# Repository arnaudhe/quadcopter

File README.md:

# Quadcopter

DIY quadcopter based on ESP32-WROOM

## Overview

### Architecture overview

```mermaid
  flowchart LR;
    subgraph QUADCOPTER
      BATTERY--supply-->Flight_controller
      BATTERY--supply-->GIMBAL
      HCSR04<--pulse-->ESP32
      subgraph Flight_controller
        MPU6050--I2C-->ESP32
        HMC5883L--I2C-->ESP32
        BMP280--I2C-->ESP32
        ESP32--DSHOT-->ESC
        ESP32--SPI-->SI4432
      end
      subgraph Motors
        ESC--3-->FRONT_RIGHT_MOTOR
        ESC--3-->FRONT_LEFT_MOTOR
        ESC--3-->REAR_RIGHT_MOTOR
        ESC--3-->REAR_LEFT_MOTOR
      end
      subgraph Video
        direction TB
        ESP32--PWM-->GIMBAL
        ESP32--TCP-->CAMERA
        CAMERA--Analog-->VIDEO_TX
        GIMBAL--supply-->VIDEO_TX
      end
      GPS--UART-->ESP32
    end
      subgraph Base_Station
        XBOX_REMOTE--USB-->LAPTOP
        LAPTOP<--USB-->RADIO_DONGLE
        VIDEO_RX--USB-->LAPTOP
      end
      RADIO_DONGLE-.433 MHz FSK.->SI4432
      LAPTOP-.WIFI.->ESP32
      VIDEO_TX-.5,8GHz.->VIDEO_RX
```

### Sensors

* Attitude sensing is based on MPU6050 (accelerometer + gyroscope) and HMC5883L (magnetometer), computed through a [Madgwick Filter](https://x-io.co.uk/open-source-imu-and-ahrs-algorithms/)
* Height sensing is based on vertical linear acceleration (output of attitude filter), a BMP180 (barometer) and a HCSR04 (ultrasound range sensor), computed through a [Kalman filter](https://en.wikipedia.org/wiki/Kalman_filter)
* Position sensing is base on horizontal linear acceleration (output of attitude filter) and a GPS, computed through a Kalman filter [Kalman filter](https://en.wikipedia.org/wiki/Kalman_filter)

cf. [documents](https://github.com/arnaudhe/quadcopter/tree/master/documents) for more details

### Controllers

* Attitude controller (manual mode) is based on a 4-dimensions [PID](https://en.wikipedia.org/wiki/PID_controller) (roll, pitch, yaw, height)
* Position controller (autonomous mode) is based on a 3-dimensions [PID](https://en.wikipedia.org/wiki/PID_controller) (x, y, z) which drives attitude controller

BLDC motors control is based on a commercial 4-in-1 ESC (electronic speed controller)

cf. [documents](https://github.com/arnaudhe/quadcopter/tree/master/documents) for more details

### Camera

The quadcopter is designed to support a [YI action camera](https://www.yitechnology.com/yi-action-camera), hold on a [2D Gimbal](https://hobbyking.com/fr_fr/tarot-t-2d-v2-xiaomi-yi-sports-camera-brushless-camera-gimbal-and-zyx22-controller.html).

The camera has:
* A TCP interface which supports json commands (take a picture, start recording, list files, ...)
* A streaming RTSP server which can be used for live video preview

The gimbal angles can be driven by the ESP32 through a serial interface.

### Communication

Communication between base station (computer or remote) is based on a shared data model, definied in a json file.

The data model ressources are implemented by the quadcopter and can be read/written/notified via:
* a json protocol (better for debug, high bandwith medium)
* a binary protocol (better for release, low bandwidth medium)

Two communications media are supported by the quadcopter:
* wifi (low range, hight bandwidth)
* FSK (longer range, low bandwidth)

```mermaid
  flowchart TD;
      subgraph Flight controller
      ESP32<-->WIFI;
      ESP32<-->RADIO;
      end
      WIFI--TCP/JSON-->CAMERA;
      CAMERA--Analog Video-->VTX
      VTX-->BASE_STATION
      WIFI<--UDP/JSON-->BASE_STATION
      RADIO<--FSK/BINARY-->BASE_STATION
```

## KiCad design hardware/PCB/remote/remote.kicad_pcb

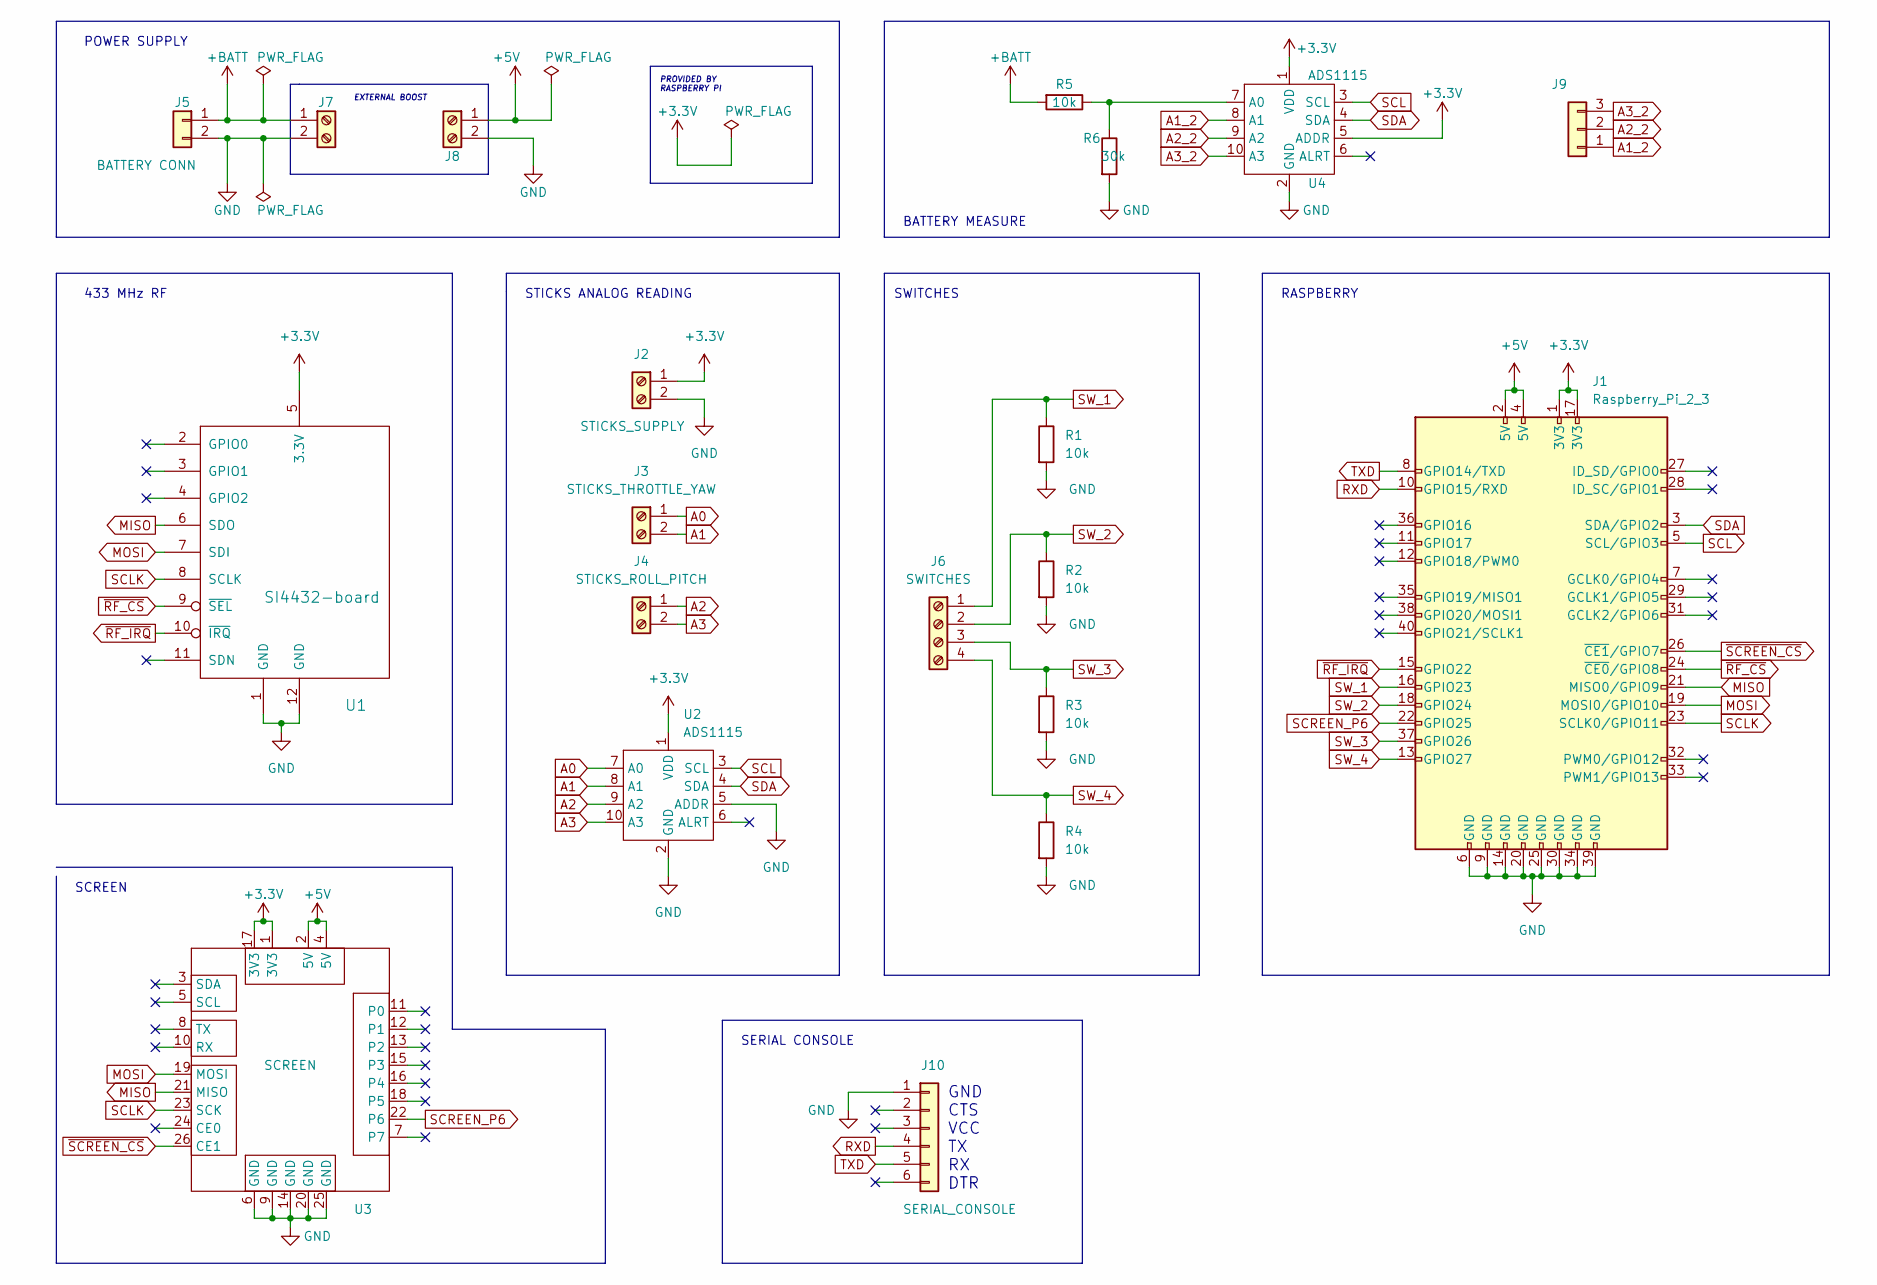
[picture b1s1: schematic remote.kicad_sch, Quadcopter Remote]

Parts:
J1: Raspberry_Pi_2_3; Raspberry_Pi_Zero_Socketed_THT_FaceDown_MountingHoles
J2: STICKS_SUPPLY; TerminalBlock_bornier-2_P5.08mm
J3: STICKS_THROTTLE_YAW; TerminalBlock_bornier-2_P5.08mm
J4: STICKS_ROLL_PITCH; TerminalBlock_bornier-2_P5.08mm
J5: BATTERY CONN; BATTERY_CHARGER
J6: SWITCHES; TerminalBlock_bornier-4_P5.08mm
J7, J8, J9: (no value)
J10: SERIAL_CONSOLE; PinHeader_1x06_P2.54mm_Vertical
R1, R2, R3, R4, R5: 10k; R_1206_3216Metric_Pad1.30x1.75mm_HandSolder
R6: 30k; R_1206_3216Metric_Pad1.30x1.75mm_HandSolder
U1: SI4432-board
U2, U4: ADS1115
U3: SCREEN; PinHeader_2x13_P2.54mm_Vertical

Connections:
+3V3: J1.1 (3V3), J1.17 (3V3), J2.1, U1.5 (3.3V), U2.1 (VDD), U3.1 (3V3), U3.17 (3V3), U4.1 (VDD), U4.5 (ADDR)
+5V: J1.2 (5V), J1.4 (5V), J8.1, U3.2 (5V), U3.4 (5V)
+BATT: J5.1, J7.1, R5.2
A0: J3.1, U2.7 (A0)
A1: J3.2, U2.8 (A1)
A1_2: J9.1, U4.8 (A1)
A2: J4.1, U2.9 (A2)
A2_2: J9.2, U4.9 (A2)
A3: J4.2, U2.10 (A3)
A3_2: J9.3, U4.10 (A3)
GND: J1.6 (GND), J1.9 (GND), J1.14 (GND), J1.20 (GND), J1.25 (GND), J1.30 (GND), J1.34 (GND), J1.39 (GND), J2.2, J5.2, J7.2, J8.2, J10.1, R1.2, R2.2, R3.2, R4.2, R6.2, U1.1 (GND), U1.12 (GND), U2.2 (GND), U2.5 (ADDR), U3.6 (GND), U3.9 (GND), U3.14 (GND), U3.20 (GND), U3.25 (GND), U4.2 (GND)
MISO: J1.21 (MISO0/GPIO9), U1.6 (SDO), U3.21 (MISO)
MOSI: J1.19 (MOSI0/GPIO10), U1.7 (SDI), U3.19 (MOSI)
unnamed: R5.1, R6.1, U4.7 (A0)
RXD: J1.10 (GPIO15/RXD), J10.4
SCL: J1.5 (SCL/GPIO3), U2.3 (SCL), U4.3 (SCL)
SCLK: J1.23 (SCLK0/GPIO11), U1.8 (SCLK), U3.23 (SCK)
SCREEN_P6: J1.22 (GPIO25), U3.22 (P6)
SDA: J1.3 (SDA/GPIO2), U2.4 (SDA), U4.4 (SDA)
SW_1: J1.16 (GPIO23), J6.1, R1.1
SW_2: J1.18 (GPIO24), J6.2, R2.1
SW_3: J1.37 (GPIO26), J6.3, R3.1
SW_4: J1.13 (GPIO27), J6.4, R4.1
TXD: J1.8 (GPIO14/TXD), J10.5
~RF_CS: J1.24 (~CE0/GPIO8), U1.9 (~SEL)
~RF_IRQ: J1.15 (GPIO22), U1.10 (~IRQ)
~SCREEN_CS: J1.26 (~CE1/GPIO7), U3.26 (CE1)

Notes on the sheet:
SERIAL CONSOLE
GND CTS VCC TX RX DTR
EXTERNAL BOOST
SWITCHES
BATTERY MEASURE
PROVIDED BY RASPBERRY PI
STICKS ANALOG READING
SCREEN
RASPBERRY
POWER SUPPLY
433 MHz RF

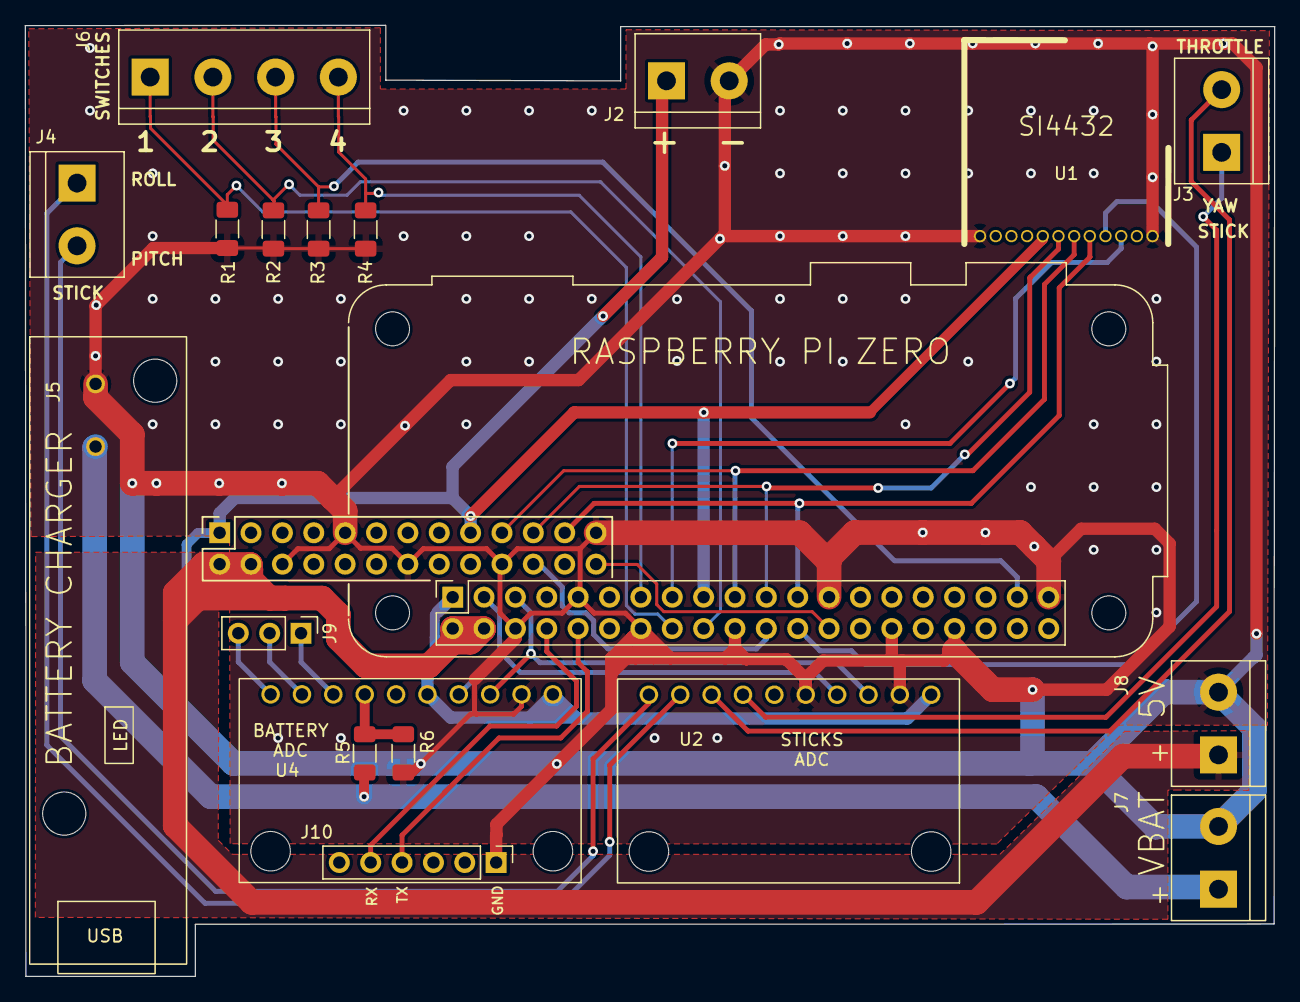
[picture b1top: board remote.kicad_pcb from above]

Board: 2 copper layers, 101.2 x 77.0 mm, 20 parts (1 on the bottom side), 27 nets.

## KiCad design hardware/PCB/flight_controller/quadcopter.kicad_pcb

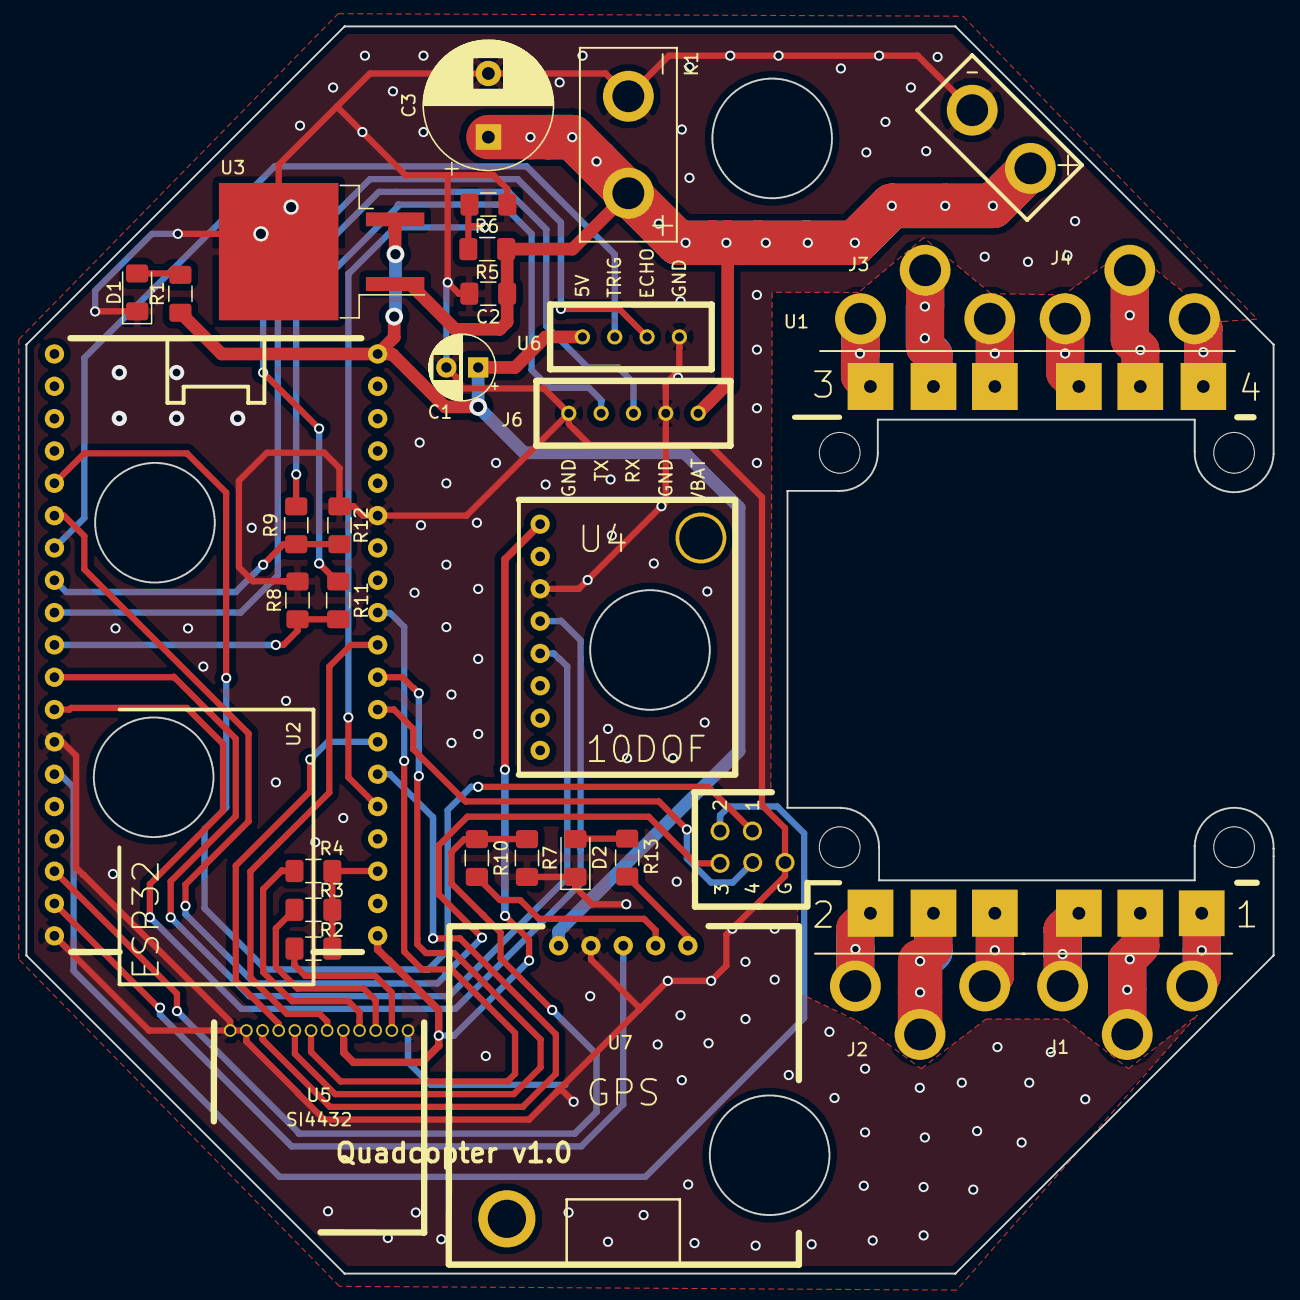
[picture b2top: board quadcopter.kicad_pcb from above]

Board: 2 copper layers, 98.0 x 98.0 mm, 31 parts (0 on the bottom side), 44 nets.

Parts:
C1: 22u; CP_Radial_D5.0mm_P2.50mm
C2: 470n; C_1206_3216Metric_Pad1.42x1.75mm_HandSolder
C3: 470u; CP_Radial_D10.0mm_P5.00mm
D1, D2: LED; LED_1206_3216Metric_Pad1.42x1.75mm_HandSolder
J1, J2, J3, J4: CONN-MOTOR; motor-connector
J6: GIMBAL
K1: BATTERY; battery-connector
R1, R13: 1k; R_1206_3216Metric_Pad1.42x1.75mm_HandSolder
R2, R3, R4: 0; R_1206_3216Metric_Pad1.42x1.75mm_HandSolder
R5: 30k; R_1206_3216Metric_Pad1.42x1.75mm_HandSolder
R6, R10, R11, R12: 10k; R_1206_3216Metric_Pad1.42x1.75mm_HandSolder
R7, R8, R9: 20k; R_1206_3216Metric_Pad1.42x1.75mm_HandSolder
U1: ESC
U2: ESP-WROOM-32-board; ESP32-VROOM-board
U3: LM2936-5.0; TO-263-2
U4: 10DOF
U5: SI4432-board
U6: HC-SR04
U7: GPS

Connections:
+3V3: U2.1, U4.1, U5.5
+5V: C1.1, R1.1, U2.19, U3.3, U6.1, U7.1
+BATT: C2.1, C3.1, J6.1, K1.1, R5.1, U1.1, U3.1
ESC_CMD1: U1.16, U2.24
ESC_CMD2: U1.17, U2.33
ESC_CMD3: U1.18, U2.25
ESC_CMD4: U1.19, U2.8
GIMBAL_RX: J6.3, U2.28
GIMBAL_TX: R9.1, R12.2, U2.27
GND: C1.2, C2.2, C3.2, D1.1, D2.1, J6.2, J6.5, K1.2, R6.2, R7.2, R8.2, R9.2, U1.2, U1.15, U2.14, U2.32, U2.38, U3.2, U4.3, U5.1, U5.11, U5.12, U6.4, U7.4
GPS_RX: U2.37, U7.3
GPS_TX: R7.1, R10.2, U2.36
HC-SR04_ECHO: R8.1, R11.2, U2.29
HC-SR04_TRIG: U2.26, U6.2
MEAS_BATT: R5.2, R6.1, U2.5
unnamed: D1.2, R1.2
unnamed: D2.2, R13.2
unnamed: J1.1, U1.3
unnamed: J1.2, U1.4
unnamed: J1.3, U1.5
unnamed: J2.1, U1.6
unnamed: J2.2, U1.7
unnamed: J2.3, U1.8
unnamed: J3.1, U1.9
unnamed: J3.2, U1.10
unnamed: J3.3, U1.11
unnamed: J4.1, U1.12
unnamed: J4.2, U1.13
unnamed: J4.3, U1.14
unnamed: J6.4, R12.1
unnamed: R2.1, U5.2
unnamed: R3.1, U5.3
unnamed: R4.1, U5.4
unnamed: R10.1, U7.2
unnamed: R11.1, U6.3
unnamed: R13.1, U7.5
SCK: U2.9, U5.8
SCL: U2.31, U4.4
SDA: U2.30, U4.5
SDI: U2.11, U5.7
SDO: U2.10, U5.6
SI4432_GPIO: R2.2, R3.2, R4.2, U2.3
~SI4432_IRQ: U2.6, U5.10
~SI4432_SEL: U2.7, U5.9

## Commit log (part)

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2021-11-03 [periodic task] Add log with actual measured task frequency every 10 sec
2021-11-03 [pulse] Fix timer configuration
2021-11-03 [.gitignore] Add pycache
2021-11-03 [base station logger] Convert logger to a class
2021-11-03 [base station] Deep refactoring to have gui, logging and xbox controller modules
2021-11-04 [tests] Add gps and filters testing notebooks
2021-11-11 [UART] Use project custom queue
    and move queue template functions into header file, add a typedef for freeRTOS queue handle to avoid using it outside this wrapper, add a constructor based on a queue handle, add an "empty" function 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
2021-11-11 [DATA] Use filesystem to read data model
    and upload the storage image folder each time the ESP32 is flashed
2021-11-11 [GPS] Add serial into main
    Opening port and configuring pattern detection (no callback for now)
2021-11-11 [NMEA] Add NMEA controller into main
    and plug it with registry and uart pattern detection callback
2021-11-11 [NMEA] Add new NMEA controller class
    In order to parse NMEA sequence and then store GPS data in the registry
2021-11-11 [LOG] Add verbose logging
    and fix "debug" prefix (W -> D)
2021-11-11 [REGISRTY] Add double type support
    Base station, data model converter, registry and json protocol source code upgrade
2021-11-11 [UART] Use project custom logging
    and increase task stack to handle this new logging
2021-11-11 [NMEA] Use project custom logging
    and increase task stack to handle this new logging
2021-11-11 [data model] update build system to use common data_model
2021-11-11 [NMEA] Move parsing to dedicated class in utils
2021-11-11 [GPS] Move NMEA_controller to GPS in HAL layer
2021-11-11 [GPS] Init UART and start pattern matcher from GPS class
2021-11-11 [GPS] Fill data model resources with parsed NMEA data
2021-11-11 [UART] Formatting
2021-11-11 Fix build in data recording mode
2021-11-11 [motors] Add dedicated motor_controller for manual motor control
2021-11-11 [PID] Increase D-term low-pass filtering
2021-11-11 [main] Set explicit control.phase registry initialization
2021-11-11 [rate ctrl] PID tuning
2021-11-18 [setup] init submodules in setup
2021-11-18 [data model] Data model reworking
2021-11-18 [data model] Add sensors to data model
2021-11-18 [base station] Fix displayed widgets value after loading
2021-11-18 [base station] Fix return type on read command error
2021-11-19 [pid] remove debug as it is replaced by telemetry
2021-11-19 [data model] Add string ressource support
2021-11-19 [UART] Improve naming, formatting and log levels
2021-11-19 [uart] fix GPS decoding error by preventing flushing received following bytes at pattern detection
2022-01-05 [telemetry] add telemetry sending over UDP
2022-01-05 [base station] connect telemetry and scope to make some magic
2022-01-14 [scope] Improve config loading
2022-01-14 [sdkconfig] Fix monitor baudrate to 921600
2022-01-14 [sdkconfig] Increase RTOS timer service queue length
2022-01-14 [task] Distribute tasks to both core 0 and core 1
2022-01-14 [gyro] Move gyro calibration sequence after init (when drone don't move)
2022-01-14 [uart] tune queues length and fix pattern detector
2022-01-14 [height ctlr] Fix bad registry ressource key
2022-01-14 [data model] Expose PID commands in data model
2022-01-14 [base station] Add scope configs
2022-01-14 [vscode] Fix build problem matcher config
2022-01-24 Remove non real-time critical functions from RAM
2022-01-24 [registry] Add direct handle to resource getter for faster access, without key lookup
2022-01-24 [attitude ctrl] Fix invalid min and max PID output commands
2022-01-24 [PID] Replace error derivate by input derivate to ignore setpoints steps
2022-01-24 [telemetry] Bulk telemetry data into one UDP datagram if period is too fast
2022-01-24 [attitude / rate] PID tuning
2022-01-24 [vscode] Use serial port from settings for flash and monitor tasks
2022-01-24 [scope] Add sensors (gyroscope and accelerometer) telemetry config
2022-01-27 [scope] Use more colors
2022-01-27 [base station] Split in modules and add option to write telemetry data to file
2022-01-27 [attitude ctrl] Update tuning
2022-01-27 [base station] Update python requirements
2022-01-27 [rate ctlr] Set static RPM notch filter
2022-01-27 [rate ctlr] Fix bad gyro calibration correction
2022-01-27 [filters] Update slew rate filter
2022-01-27 [rate ctlr] Add accelero bias correction with calibration
2022-01-27 [filters] Add unit tests
2022-01-27 [env] Add base_station folder to dev environment path
2022-01-27 [PID] Reduce default (rate control) min and max commands
2022-01-27 [euler observer] Increase observer gain for faster drift correction
2022-01-27 [height ctlr] First approximative tuning
2022-01-27 [height ctlr] Fill barometer and ultrasound measures in registry for telemetry
2022-02-01 [cmake] remove trailing spaces
2022-02-01 [PID] Add state reset method and call it when controllers are disabled
2022-02-01 [height ctlr] TEMPORARY - Use ultrasound sensor height instead of Kalman filter output
2022-02-01 [rate ctlr] Use static gyro calibration
2022-02-01 [RC] Add basic continuous stream radio control over UDP
2022-02-01 [scope] Enable FFT to gyro to measure filters effets
2022-02-05 [SPI] First implementaion
2022-02-05 [base station] Exit with error if remote asked but not plugged
2022-02-05 [radio command] Set yaw and throttle commands received on rc
2022-02-11 [GPS] Fix memory leak in NMEA parser
2022-02-13 [base station] Add basic GUI generation script with video stream display
2022-02-16 [GPIO] Fix gpio init for pins 33-36
2022-02-16 [SI4432] Improve driver with IRQ management
2022-02-16 [main] Add FSK reception in main loop
2022-02-18 [HCSR04] Stop limiting the sensor output to 1m
2022-02-18 [BMP280] Reduce low-pass filter
2022-02-18 [height observer] Remove zero-velocity detector
2022-02-18 [height observer] Reduce output order to 1 (only barometer)
2022-02-18 [scope] Update height scope config
2022-02-18 [docs] Add SI4432 datasheets
2022-03-01 [tools] Add requirements file for python package dependencies
2022-03-01 [vscode] Add tools folder in workspace
2022-03-01 [battery] Add periodic battery monitoring
2022-03-03 [SI4432] Tune config for working RX
2022-03-03 [SI4432] Add RSSI reading function
2022-03-03 [base station] Add radio dongle module
2022-03-03 [battery] tune ADC measure after divider increased
2022-03-03 [battery] Increase battery voltage log resolution
2022-03-08 [protocol] Move binary protocol encoder/decoder to base station
2022-03-08 [base station] Rework architecture to work over a udp or radio broker
2022-03-08 [data model] Fix some binary ressource ids
2022-03-08 [soft] Create dedicated class for periodic heartbeat
2022-03-10 [base station] Add some docstrings
2022-03-10 [Heartbeat] Use radio broker with proper channel for heartbeat sending
2022-03-10 [radio command] Make UDP reception non-blocking to enable listening on radio
2022-03-10 [broker] Centralize broker channels and use thoses definitions for UDP
2022-03-10 [radio command] Improve sticks reading and add non-linear rates
2022-03-10 [radio] Stabilize python radio driver and broker
2022-03-10 [height control] Replace default mode from manual to speed control
2022-03-10 [Si4432] Reduce log verbosity on frame receiving
2022-03-10 [attitude ctrl] Update PIDs tuning with new propellers
2022-03-10 [README] Replace ASCII-scheme with mermaid
2022-03-10 [README] Update architecture schema
2022-03-12 [README] Add architecture overview graph
2022-03-14 [scope] Add vertical speed to height scope config
2022-03-26 [radio] Add CRC16 frame integrity check
2022-03-26 [base station] Fix periodic worker instanciation
2022-03-26 [height observer] Tuning & restoring zero velocity detector to improve stability
2022-03-27 [base station] Add method to get radio link quality in percents
2022-03-31 [radio] Remove broker mechanisms from radio and convert to lower level abstraction layer
2022-03-31 [udp] Convert UDP to lower level os abstraction layer
2022-03-31 [crc16] Add method to update with one-byte input
2022-03-31 [broker] Create broker for UDP and radio communication channels multiplexing
2022-03-31 [Heartbeat] Use broker instead of out-of-date Udp server and radio broker
2022-03-31 [data recorder] Move to workers folder
2022-03-31 [json protocol] make it stateless by removing registration to out-of-date UDP server
2022-03-31 [binary protocol] Add binary data model protocol manager
2022-03-31 [data model ctrl] Centralize json and binary requests handling in ctlr which relies on broker
2022-03-31 [main] Suppress unused variables warnings
2022-04-01 [tests] Refactor soft tests and add binary protocol tests
2022-04-01 [tasks] tune priority and stack sizes
2022-04-01 [Heartbeat] Increase period to 3 sec to avoid radio collisions
2022-04-01 [protocol] Fix python float and double variables encoding
2022-04-01 [radio] Remove link quality log on each reception
2022-04-01 [radio] Add delay before exiting TX to avoid CRC errors
2022-04-02 [status] Remove not used status declaration
2022-04-02 [byte array] Add clear and replace data methods
2022-04-03 [base station] Display camera properties in GUI
2022-04-03 [wifi] Fix wifi state mangement
2022-04-03 [barometer] increase stack size
2022-04-03 [camera] Add yi action camera HAL implementation (tcp over wifi)
2022-04-03 [code] Update workspace settings
2022-04-03 [tcp] Add os-level tcp abstraction class
2022-05-01 Move base station
2022-05-01 Move data model
2022-05-01 Move 3D
2022-05-01 Move flight_controller PCB
2022-05-01 Move test & tools
2022-05-01 Move sizing
2022-05-01 [PCB] Add remote PCB v1.0
2022-05-01 Move env
2022-05-01 [vscode] Improve C/C++ config
2022-05-01 [GPS] Fix missing initializer warning
2022-05-02 [3D] Add quadcopter antennas holders
2022-05-02 [3D] Add remote top
2022-05-19 Add radio_command skeleton
2022-05-19 Add radio_command to code workspace
2022-05-24 [radio command] Add iio ADC abstraction layer
2022-05-24 [radio command] Fix sticks ADC channels
2022-05-24 [radio command] Fix I2C port
2022-05-24 [radio command] Add I2C bulk registers read and write method
2022-05-24 [radio command] Fix SPI unused include
2022-05-24 [radio command] Update method call to get sticks command
2022-05-24 [radio command] Fix buttons GPIO mapping
2022-05-24 [radio command] Add ADS1115 ADC over I2C implementation
2022-05-24 [base station] Fix out-of-date methods call in radio test snippet
2022-05-24 [radio command] Add basic periodic radio sending
2022-05-30 [radio_command] Add radio layer and basic implementation
2022-06-11 [3D] Add landing system pieces
2022-06-17 [rc] Import libjpeg dependency in sysroot
2022-06-17 [rc] Add jpeg decoding class based on libjpeg
2022-06-17 [rc] Add framebuffer abstraction class to display image on screen
2022-06-17 [rc] Add task abstraction class based on pthread dep
2022-06-17 [rc] Start parallel video, rc and battery workers at startup
2022-06-17 [rc] Fix gpio shared memory access denied permission
2022-06-17 [rc] open I2C device in constructor instead of dedicated method
2022-06-17 [rc] Remove attribute initialization in class declaration
2022-06-17 [rc] Add video feedback applicative worker
2022-06-17 [rc] Change vscode C/C++ compiler path on linux
2022-06-17 [3D] Add remote backcover
2022-06-17 [3D] Add remote usb hub and batery support
2022-06-17 Align radio frames staructure with length
2022-06-19 [rc] Add PixMap mathods to display text, rectangle, and color filling
2022-06-19 [rc] Enter in range test mode when pressing both bottom buttons at startup
2022-06-19 [flight controller] Add state machine utility base class
2022-06-19 [fc] Send status through rc channel every second
2022-06-19 [flight controller] Add periodic task method to on-demand execute run method
2022-06-19 [fc + rc] Add camera record request and gimbal tilt in radio commands
2022-06-19 [rc] Add action to start camera recording with bottom right button
2022-06-23 [flight controller] Reduce applicative tasks stack size
2022-06-23 [flight controller - radio] Add mutex on tx and rx packet in driver
2022-06-25 [rc] Transform si4432 driver to state machine for tx/rx
2022-06-25 [rc] Get and display quadcopter telemetry
2022-06-25 [flight controller] Improve timings for radio rx/tx
2022-07-25 [rc] Remote battery measurement
2022-07-25 [rc] Fix sticks direction
2022-07-27 [3D] Add exported stl models
